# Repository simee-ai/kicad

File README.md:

# simee-ai/kicad

Builds of [KiCad](https://www.kicad.org) and of the GNU toolchains for AVR and Arm microcontrollers, published as
this repository's releases.

## Licences

- `cli-<version>-<n>`: a trimmed `kicad-cli` from that KiCad release, with KiCad's own files built from the official
  release or from this repository's `simee/<version>` branch (KiCad's source with simee's changes, named in the
  release notes by commit). KiCad is GPL-3.0-or-later (its `LICENSE.README` lists the third-party code it includes),
  and so is each bundle as a whole. The bundled third-party libraries keep their own licences: each bundle's
  `THIRD-PARTY.txt` names them, with their licence files beside it. The Windows bundle also holds Microsoft's
  Visual C++ runtime, shipped as Visual Studio 2022 Distributable Code under Microsoft's terms.
- `avr-gcc-<version>-<n>`: binutils and GCC (GPL-3.0-or-later; libgcc under the GCC Runtime Library Exception, so
  firmware built with it carries no GPL obligation), GMP, MPFR and MPC (LGPL-3.0-or-later) and avr-libc
  (BSD-3-Clause).
- `arm-gcc-<version>-<n>`: Arm GNU Toolchain: binutils and GCC (GPL-3.0-or-later; libgcc and libstdc++ under the
  GCC Runtime Library Exception), newlib (the BSD-style licences its `COPYING.NEWLIB` lists), GMP, MPFR and MPC
  (LGPL-3.0-or-later), isl (MIT), libiconv (LGPL-2.1-or-later) and zstd (BSD-3-Clause).

Each toolchain archive holds the licence files of its components in `share/doc/` and a `THIRD-PARTY.txt` naming
them. Every release carries the complete corresponding source of everything it ships, attached to the release
itself, rather than a written offer.

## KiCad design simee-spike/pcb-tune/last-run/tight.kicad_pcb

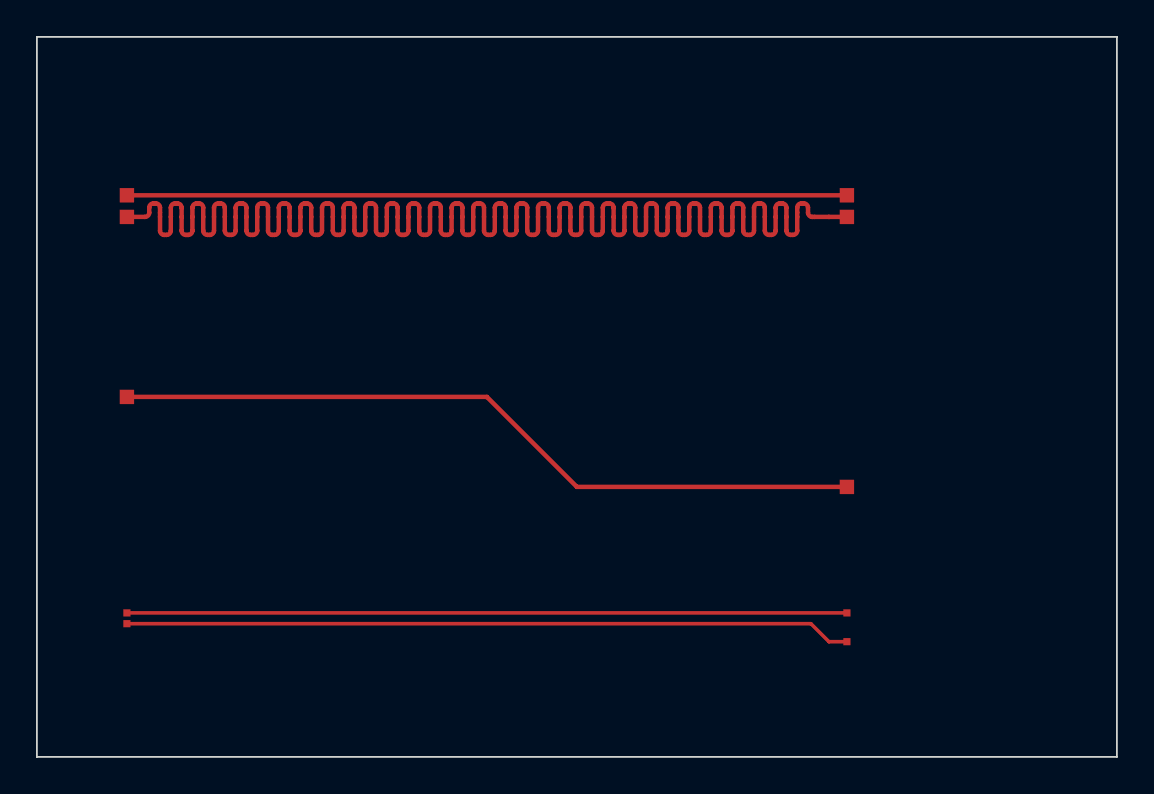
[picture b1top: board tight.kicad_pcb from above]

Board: 2 copper layers, 60.0 x 40.0 mm, 10 parts (0 on the bottom side), 5 nets.

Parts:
TP1, TP2, TP3, TP4, TP5, TP6, TP7, TP8, TP9, TP10: TP

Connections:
OBST: TP5.1, TP6.1
SIG_A: TP1.1, TP2.1
SIG_B: TP3.1, TP4.1
USB_N: TP9.1, TP10.1
USB_P: TP7.1, TP8.1
